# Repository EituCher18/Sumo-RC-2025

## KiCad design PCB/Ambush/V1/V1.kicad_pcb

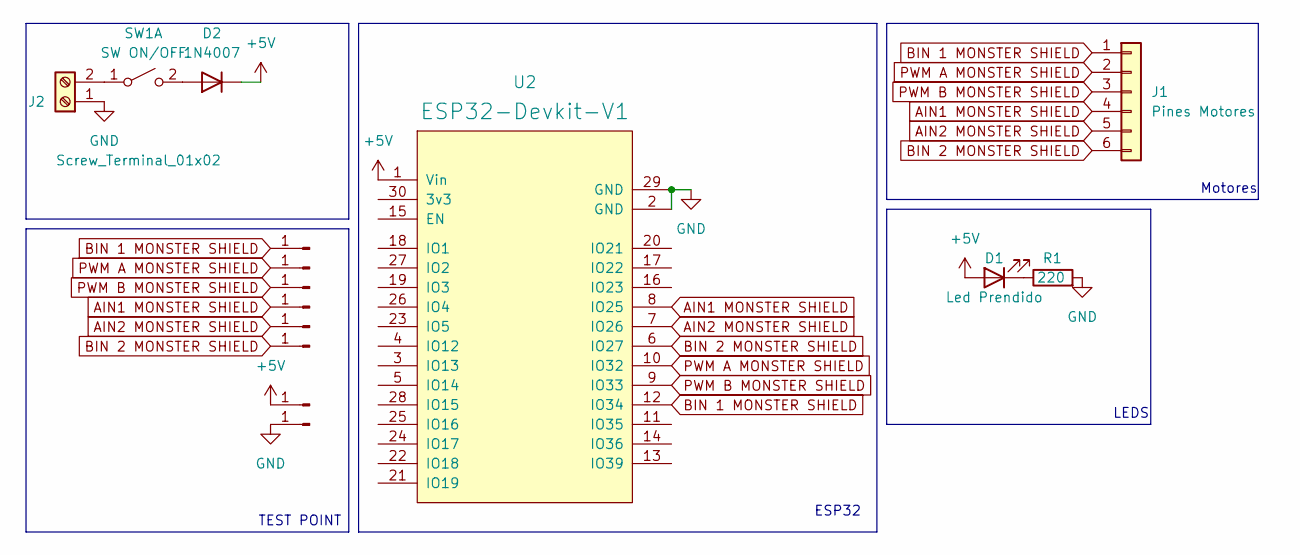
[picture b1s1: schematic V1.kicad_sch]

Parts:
D1: Led Prendido; LED_D5.0mm
D2: 1N4007; D_DO-41_SOD81_P10.16mm_Horizontal
J1: Pines Motores; Molex_KK-254_AE-6410-06A_1x06_P2.54mm_Vertical
J2: Screw_Terminal_01x02; TerminalBlock_bornier-2_P5.08mm
J3, J4, J5, J6, J7, J8, J9, J10: Conn_01x01_Pin; PinHeader_1x01_P2.54mm_Vertical
R1: 220; R_Axial_DIN0207_L6.3mm_D2.5mm_P10.16mm_Horizontal
SW1: SW ON/OFF; TerminalBlock_bornier-2_P5.08mm
U2: ESP32-Devkit-V1; DOIT_ESP32_Devkit_mirko

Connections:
+5V: D1.2 (A), D2.1 (K), J9.1, U2.1 (Vin)
AIN1 MONSTER SHIELD: J1.4, J6.1, U2.8 (IO25)
AIN2 MONSTER SHIELD: J1.5, J7.1, U2.7 (IO26)
BIN 1 MONSTER SHIELD: J1.1, J3.1, U2.12 (IO34)
BIN 2 MONSTER SHIELD: J1.6, J8.1, U2.6 (IO27)
GND: J2.1, J10.1, R1.2, U2.2 (GND), U2.29 (GND)
unnamed: D1.1 (K), R1.1
unnamed: D2.2 (A), SW1.2 (B)
unnamed: J2.2, SW1.1 (A)
PWM A MONSTER SHIELD: J1.2, J4.1, U2.10 (IO32)
PWM B MONSTER SHIELD: J1.3, J5.1, U2.9 (IO33)

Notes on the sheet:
LEDS
TEST POINT
ESP32
Motores

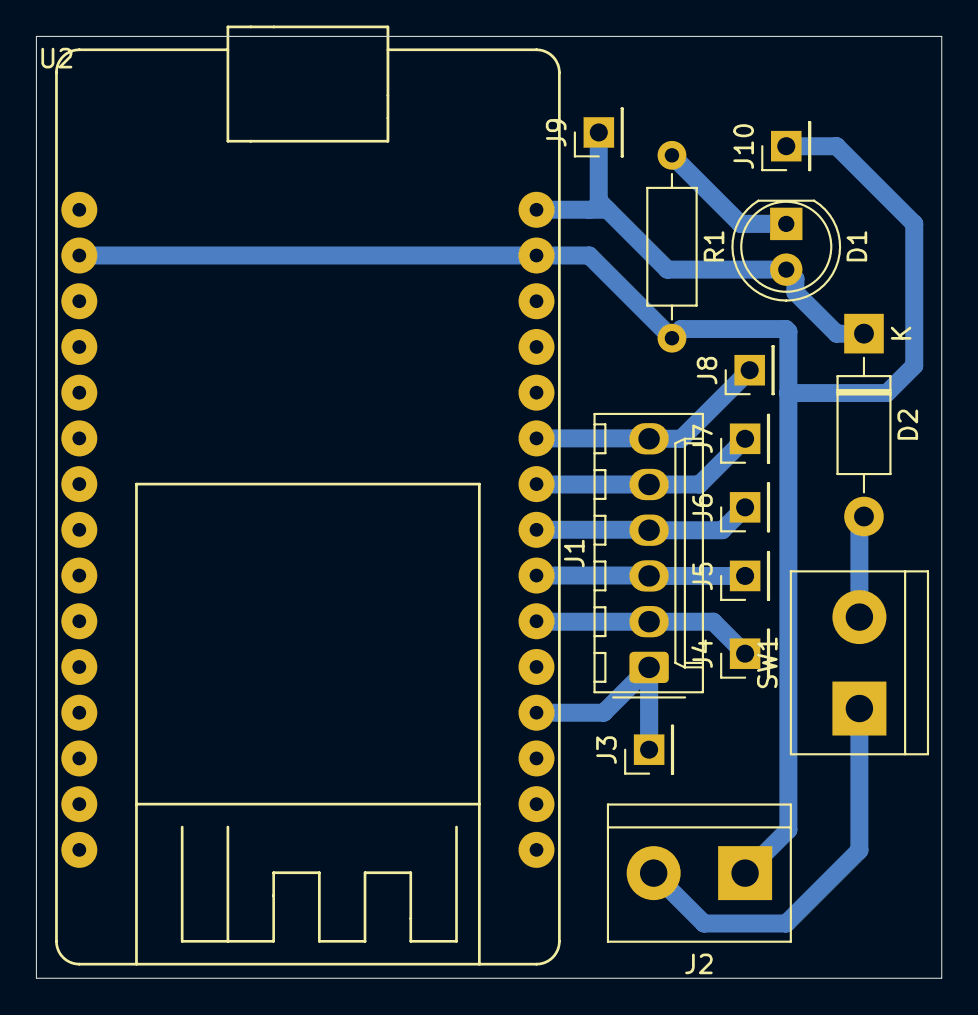
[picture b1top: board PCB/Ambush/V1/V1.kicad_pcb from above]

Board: 2 copper layers, 50.3 x 52.3 mm, 15 parts (0 on the bottom side), 11 nets.

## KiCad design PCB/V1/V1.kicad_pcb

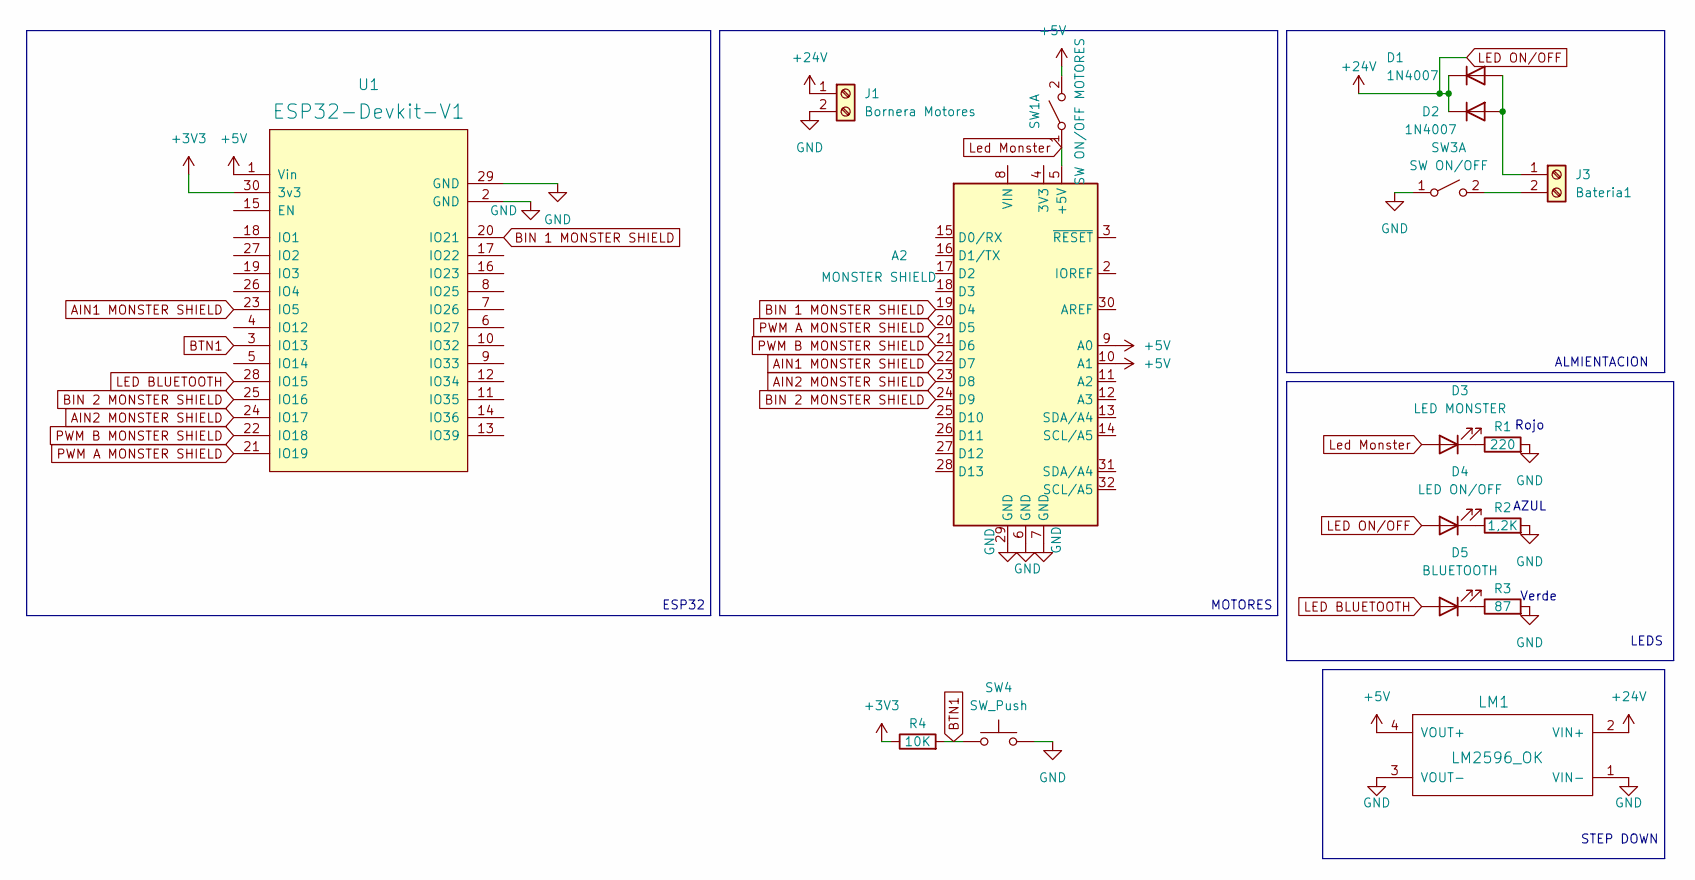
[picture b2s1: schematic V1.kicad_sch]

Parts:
A2: MONSTER SHIELD; Arduino_UNO_R3
D1, D2: 1N4007; D_DO-41_SOD81_P10.16mm_Horizontal
D3: LED MONSTER; LED_D5.0mm_Horizontal_O1.27mm_Z3.0mm
D4: LED ON/OFF; LED_D5.0mm_Horizontal_O1.27mm_Z3.0mm
D5: BLUETOOTH; Molex_KK-254_AE-6410-02A_1x02_P2.54mm_Vertical
J1: Bornera Motores; TerminalBlock_bornier-2_P5.08mm
J3: Bateria1; AMASS_XT60-M_1x02_P7.20mm_Vertical
LM1: LM2596_OK; LM2596_correctedMeas
R1: 220; R_Axial_DIN0207_L6.3mm_D2.5mm_P10.16mm_Horizontal
R2: 1,2K; R_Axial_DIN0207_L6.3mm_D2.5mm_P10.16mm_Horizontal
R3: 87; R_Axial_DIN0207_L6.3mm_D2.5mm_P10.16mm_Horizontal
R4: 10K; R_Axial_DIN0207_L6.3mm_D2.5mm_P10.16mm_Horizontal
SW1: SW ON/OFF MOTORES; SW_Slide_SPDT_Angled_CK_OS102011MA1Q
SW3: SW ON/OFF; TerminalBlock_bornier-2_P5.08mm
SW4: SW_Push; TerminalBlock_bornier-2_P5.08mm
U1: ESP32-Devkit-V1; DOIT_ESP32_Devkit_mirko

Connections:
+3V3: R4.1, U1.30 (3v3)
+5V: A2.9 (A0), A2.10 (A1), LM1.4 (VOUT+), SW1.2 (B), U1.1 (Vin)
AIN1 MONSTER SHIELD: A2.22 (D7), U1.23 (IO5)
AIN2 MONSTER SHIELD: A2.23 (D8), U1.24 (IO17)
BIN 1 MONSTER SHIELD: A2.19 (D4), U1.20 (IO21)
BIN 2 MONSTER SHIELD: A2.24 (D9), U1.25 (IO16)
BTN1: R4.2, SW4.1, U1.3 (IO13)
GND: A2.6 (GND), A2.7 (GND), A2.29 (GND), J1.2, LM1.1 (VIN-), LM1.3 (VOUT-), R1.2, R2.2, R3.2, SW3.1 (A), SW4.2, U1.2 (GND), U1.29 (GND)
LED BLUETOOTH: D5.2 (A), U1.28 (IO15)
LED ON/OFF: D1.1 (K), D2.1 (K), D4.2 (A), J1.1, LM1.2 (VIN+)
Led Monster: A2.5 (+5V), D3.2 (A), SW1.1 (A)
unnamed: D1.2 (A), D2.2 (A), J3.1
unnamed: D3.1 (K), R1.1
unnamed: D4.1 (K), R2.1
unnamed: D5.1 (K), R3.1
unnamed: J3.2, SW3.2 (B)
PWM A MONSTER SHIELD: A2.20 (D5), U1.21 (IO19)
PWM B MONSTER SHIELD: A2.21 (D6), U1.22 (IO18)

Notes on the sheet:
ALMIENTACION
LEDS
AZUL
Rojo
Verde
MOTORES
ESP32
STEP DOWN

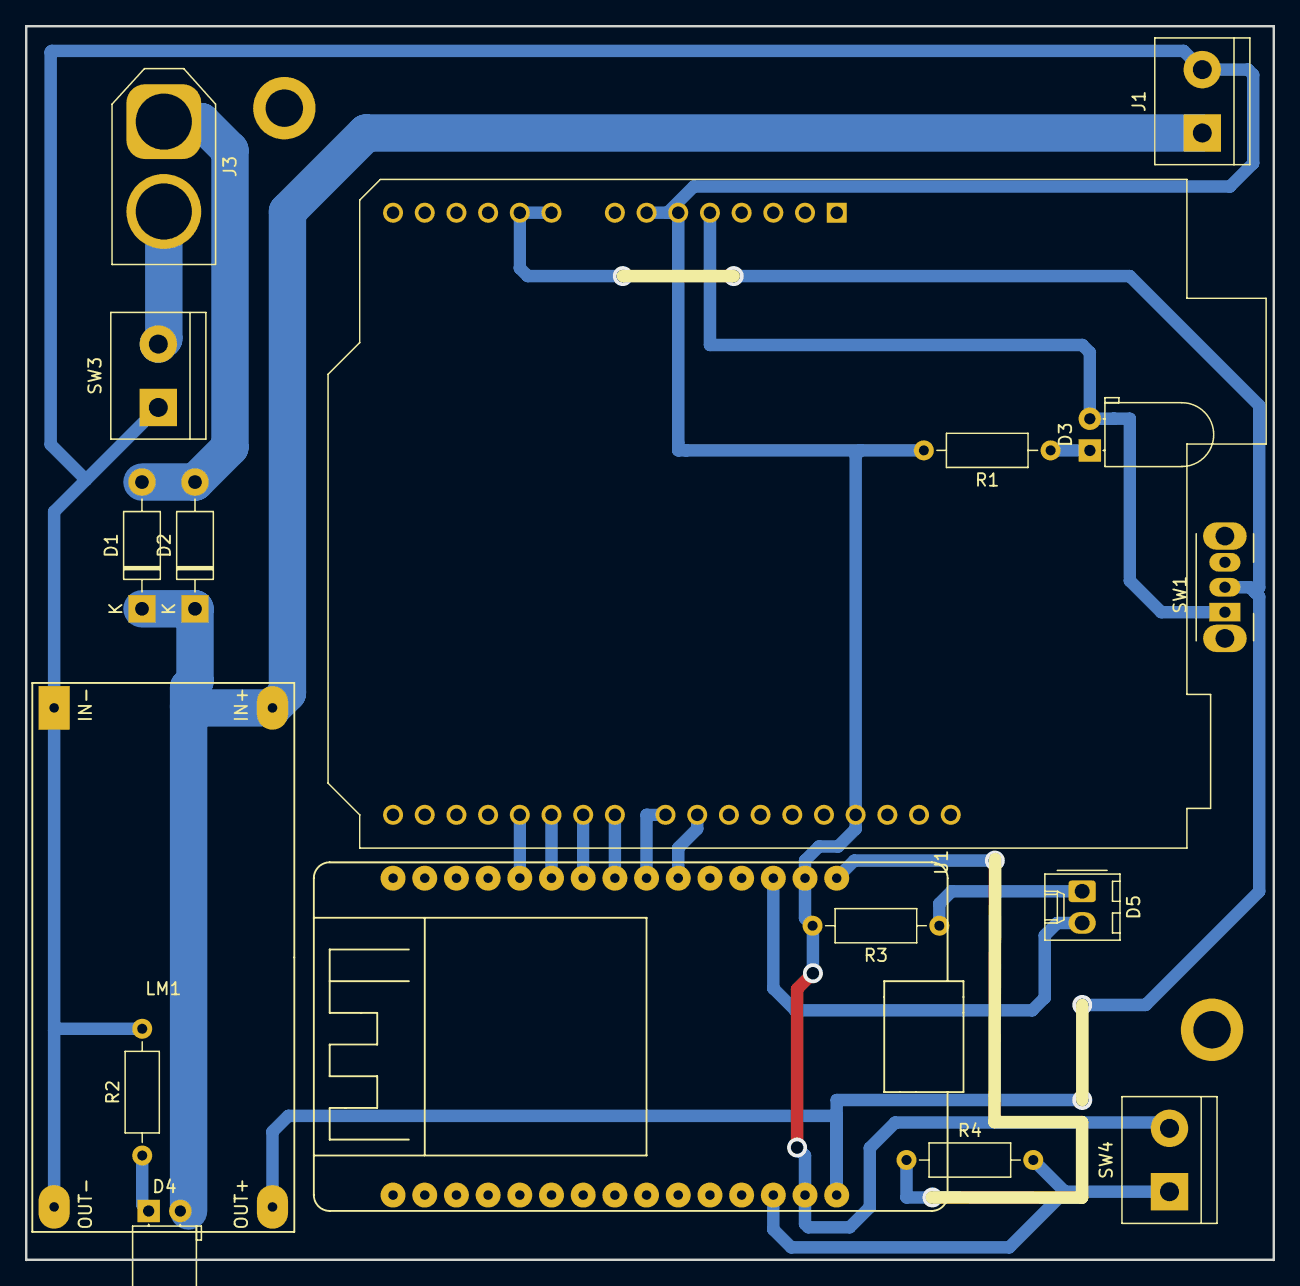
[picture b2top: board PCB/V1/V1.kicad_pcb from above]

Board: 2 copper layers, 100.0 x 98.9 mm, 17 parts (1 on the bottom side), 18 nets.

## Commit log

2024-10-29 Agregue para que se mande una sola vez el color del led
2024-10-30 En teoria terminado solo falta ver como hace los giros
2024-10-30 Placa ambush
2024-10-31 PCB Con testpoint
2024-10-31 PCB con testpoint ambush
2024-10-31 Codigo Pro
2024-10-31 Finalizar código V2 de Sumo RC
2024-10-31 Fix compilation issues
2024-10-31 Fix issue where controller can't reconnect
